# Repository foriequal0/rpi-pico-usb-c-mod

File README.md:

Raspberry Pi Pico USB-C Mod
===

This repository contains an adapter board for RPI Pico USB-C mod.
It should be compatible with all versions of RPI Pico family (Pico, Pico W, Pico W, Pico WH, Pico 2, Pico 2 W), 
although I've designed to mod a Pico 2 W.

It supports both USB 2.0 data and power, just like micro-USB did.

## BOM

* The adapter board PCB
* GCT USB4110-GF-A
* 51k Ohm 0805 resistors x2 
* Some wires

## How to build

### Make the PCB

You somehow need to make the adapter board PCB.
I've ordered through [JLCPCB](https://jlcpcb.com/). The thickness was 0.8mm.

### Solder the board

Then solder the adapter board PCB on the back of the RPI Pico.
Three pads on the adapter board should align with the RPI Pico's three pads (TP1, TP2, TP3).
It's easier to use a hot plate and solder paste.

### Solder the USB-C port

Next, solder the USB-C port on the adapter board.
It's easier to hand-solder with solder paste.

### Wire the VBUS

Finally, wire the remaining pad on the bottom-left side of the adapter board to the VBUS pin of the Raspberry Pico.

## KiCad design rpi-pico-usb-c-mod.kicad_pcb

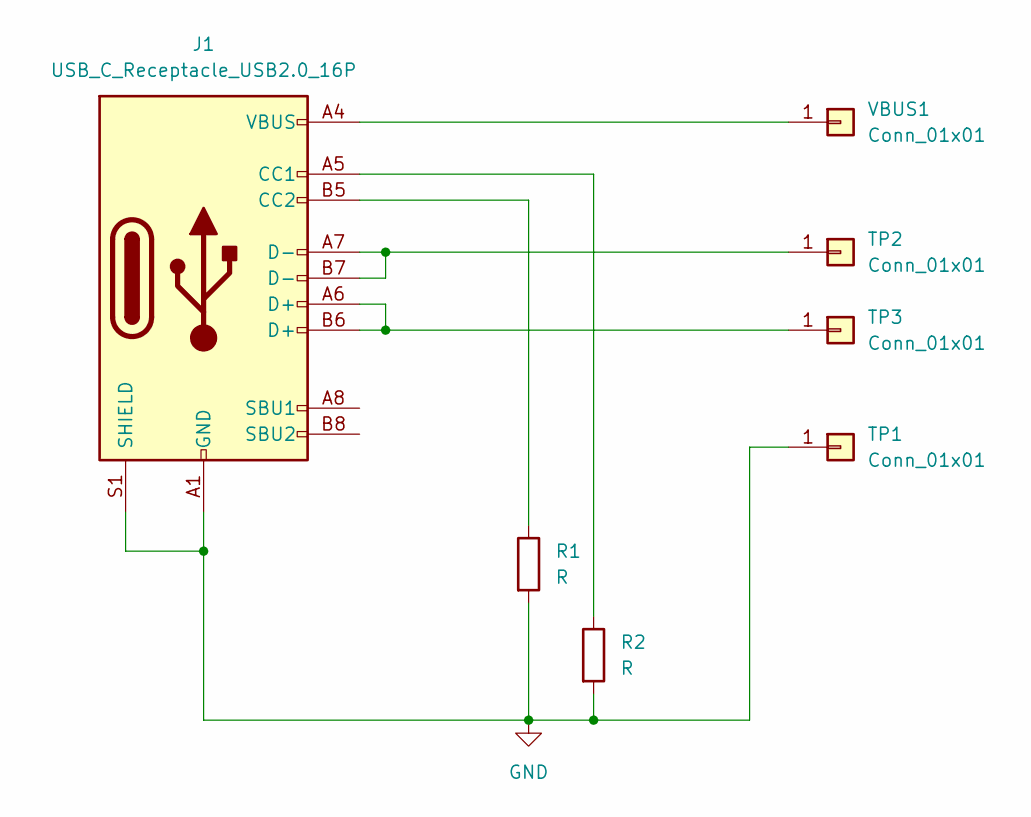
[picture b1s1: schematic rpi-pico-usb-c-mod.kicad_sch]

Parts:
J1: USB_C_Receptacle_USB2.0_16P; USB_C_Receptacle_GCT_USB4110
R1, R2: R; R_0805_2012Metric
TP1, TP2, TP3: Conn_01x01; TestPoint_Pad_1.5x1.5mm
VBUS1: Conn_01x01; TestPoint_Pad_1.5x1.5mm

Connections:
GND: J1.A1 (GND), J1.A12 (GND), J1.B1 (GND), J1.B12 (GND), J1.S1 (SHIELD), R1.2, R2.2, TP1.1
unnamed: J1.A5 (CC1), R2.1
unnamed: J1.B5 (CC2), R1.1
unnamed: J1.A7 (D-), J1.B7 (D-), TP2.1
unnamed: J1.A6 (D+), J1.B6 (D+), TP3.1
unnamed: J1.A4 (VBUS), J1.A9 (VBUS), J1.B4 (VBUS), J1.B9 (VBUS), VBUS1.1

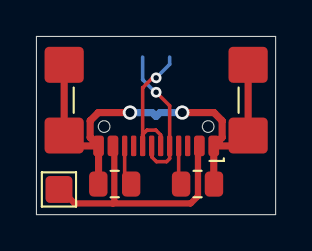
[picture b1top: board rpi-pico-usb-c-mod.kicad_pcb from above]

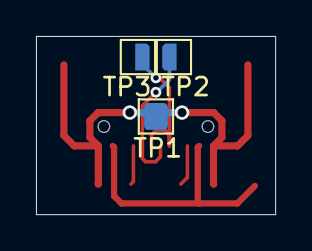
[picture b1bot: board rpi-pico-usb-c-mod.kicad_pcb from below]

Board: 2 copper layers, 13.3 x 9.9 mm, 7 parts (3 on the bottom side), 6 nets.

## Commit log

2025-04-05 publish
2025-04-06 mention usb 2.0 data and power capability
